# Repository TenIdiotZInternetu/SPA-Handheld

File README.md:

# SPA-Handheld

This is the main part of the Handheld Console project, a topic we chose for the Slovak Students' Professional Activities 2022.

All design files of the final product are contained here. The whole process of inspiration, designing PCB and 3D model and setting up the device is documented in the docx/pdf document.

## Subprojects

Task of the SPA included designing and programming the startup GUI and a game created in Pygame. Both found in the repos below.

* [**Bullet Hell (Videogame)**](https://github.com/TenIdiotZInternetu/SPA-Bullet-Hell)  
* [**GUI**](https://github.com/TenIdiotZInternetu/SPA-Bullet-Hell)

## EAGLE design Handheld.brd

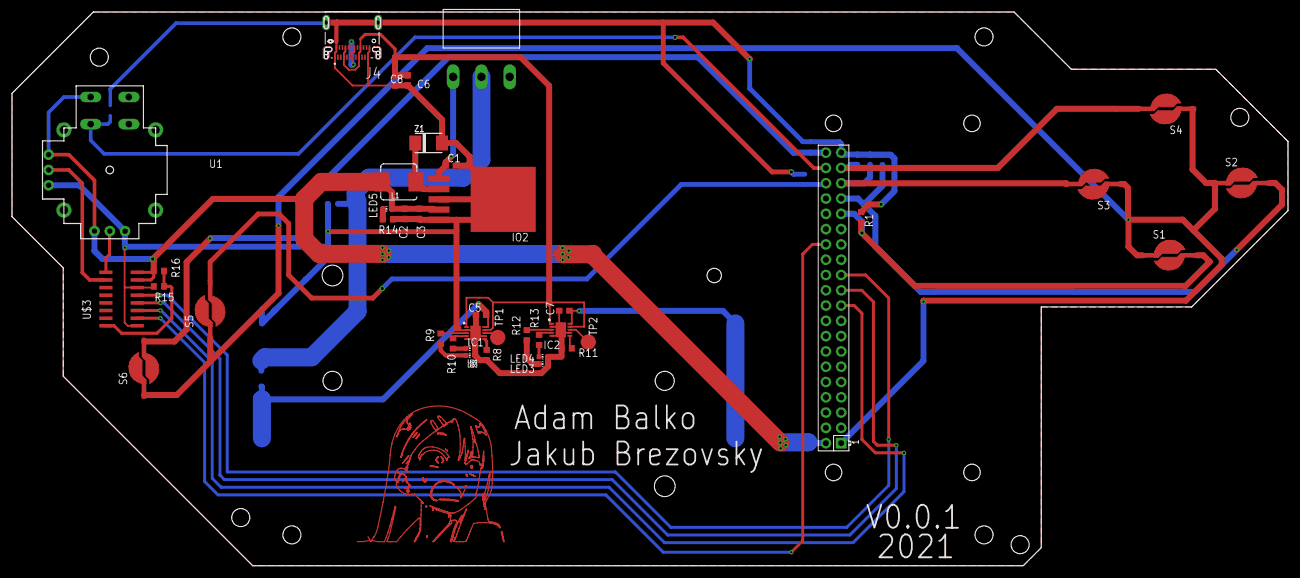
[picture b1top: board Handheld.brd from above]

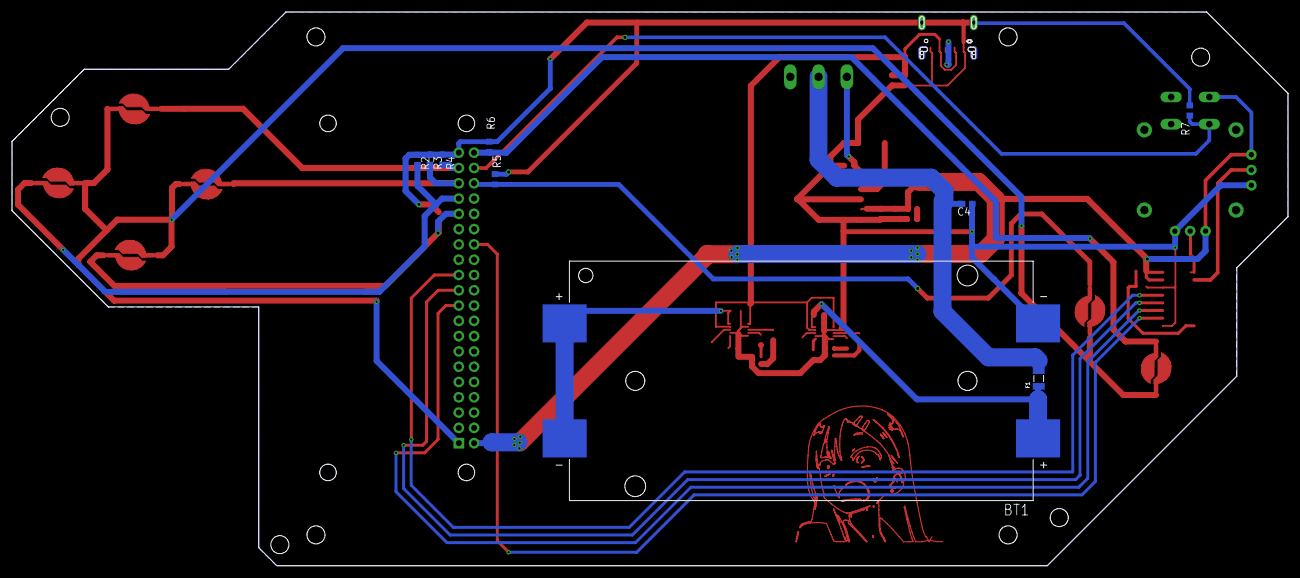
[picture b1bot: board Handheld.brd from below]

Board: 2 copper layers, 212.0 x 92.0 mm, 49 parts (9 on the bottom side), 38 nets.

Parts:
BT1: 1048P; BAT_1048P
C1: 330n; C0603
C2: 220n; C0603
C3, C5, C6, C7, C8: 100nF; C0603
C4: 100n; C0603
F1: 5A; 3413.0113.22
IC1, IC2: BQ24080DRCR; SON50P300X300X100-11N
IO2: LM2596S-5; TO263-5
J4: DX07S024JJ3R1300; JAE_DX07S024JJ3R1300
L1: 22UH; INDUCTOR_L0630
LED1, LED2, LED3, LED4, LED5: CHIP-LED0603
R1, R2, R3, R4, R5, R6, R7, R9, R10, R12, R13, R14: 470; R0603
R8, R11: 1.13k; R0603
R15: 4.7k; R0603
R16: 3k; R0603
RPI: RPI-ZERO; RASPBERRYPI_BASTELSTUBE_V13_RASPI_BOARD_B+_FULL
S1, S2, S3, S4, S5, S6: BUTTON
TP1, TP2: TPB2,54; B2,54
U1: JOYSTICKPTH; JOYSTICK
U$3: MCP3008SL; SO16
U$10: 1P2T
Z1: 1n5824; SUPRESSOR_SMAJ

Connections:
+3V3: RPI.1, S1.1, S2.1, S3.1, S4.1, S5.1, S6.1
+5V: C2.1, C3.1, IO2.4, L1.2, LED5.A, R16.1, RPI.2, U1.B1A, U1.H1, U1.V1, U$3.15, U$3.16
A: R1.2, RPI.31, S1.2
B: R2.2, RPI.33, S2.2
BAT_1: BT1.1+, C5.1, F1.1, IC1.10
BAT_2: BT1.1-, BT1.2+, C7.1, IC2.10
BAT_OUT: C1.1, IO2.1, U$10.P$1
CS: RPI.28, U$3.10
FUSE: C4.2, F1.2, U$10.P$2
GND: BT1.2-, C1.2, C2.2, C3.2, C4.1, C5.2, C6.2, C7.2, C8.2, IC1.2, IC1.5, IC1.7, IC1.11, IC2.2, IC2.5, IC2.7, IC2.11, IO2.3, IO2.5, IO2.6, J4.A1, J4.A12, J4.B1, J4.B12, J4.S1, J4.S2, LED1.A, LED2.A, LED3.A, LED4.A, R1.1, R2.1, R3.1, R4.1, R5.1, R6.1, R7.1, R8.1, R11.1, R14.2, R15.2, RPI.39, U1.H3, U1.V3, U$3.9, U$3.14, Z1.A
JS: R7.2, RPI.38, U1.B2A
MISO: RPI.21, U$3.12
MOSI: RPI.19, U$3.11
unnamed: U1.H2, U$3.1
unnamed: LED5.C, R14.1
unnamed: U1.V2, U$3.2
unnamed: IC1.6, R8.2
unnamed: IC1.4, R10.2
unnamed: IC1.3, R9.2
unnamed: LED1.C, R9.1
unnamed: LED2.C, R10.1
unnamed: IC2.6, R11.2
unnamed: IC2.4, R13.2
unnamed: IC2.3, R12.2
unnamed: LED3.C, R12.1
unnamed: LED4.C, R13.1
unnamed: IC1.8, TP1.TP
unnamed: IC2.8, TP2.TP
unnamed: IO2.2, L1.1, Z1.C
SCLK: RPI.23, U$3.13
SELECT: R6.2, RPI.40, S6.2
START: R5.2, RPI.36, S5.2
USB_IN: C6.1, C8.1, IC1.1, IC1.9, IC2.1, IC2.9, J4.A4, J4.A9, J4.B4, J4.B9
USB_OUT_3_N: J4.A7, J4.B7
USB_OUT_3_P: J4.A6, J4.B6
V_DEL: R15.1, R16.2, U$3.8
X: R3.2, RPI.35, S3.2
Y: R4.2, RPI.37, S4.2

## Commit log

2022-07-24 Create Scripts
